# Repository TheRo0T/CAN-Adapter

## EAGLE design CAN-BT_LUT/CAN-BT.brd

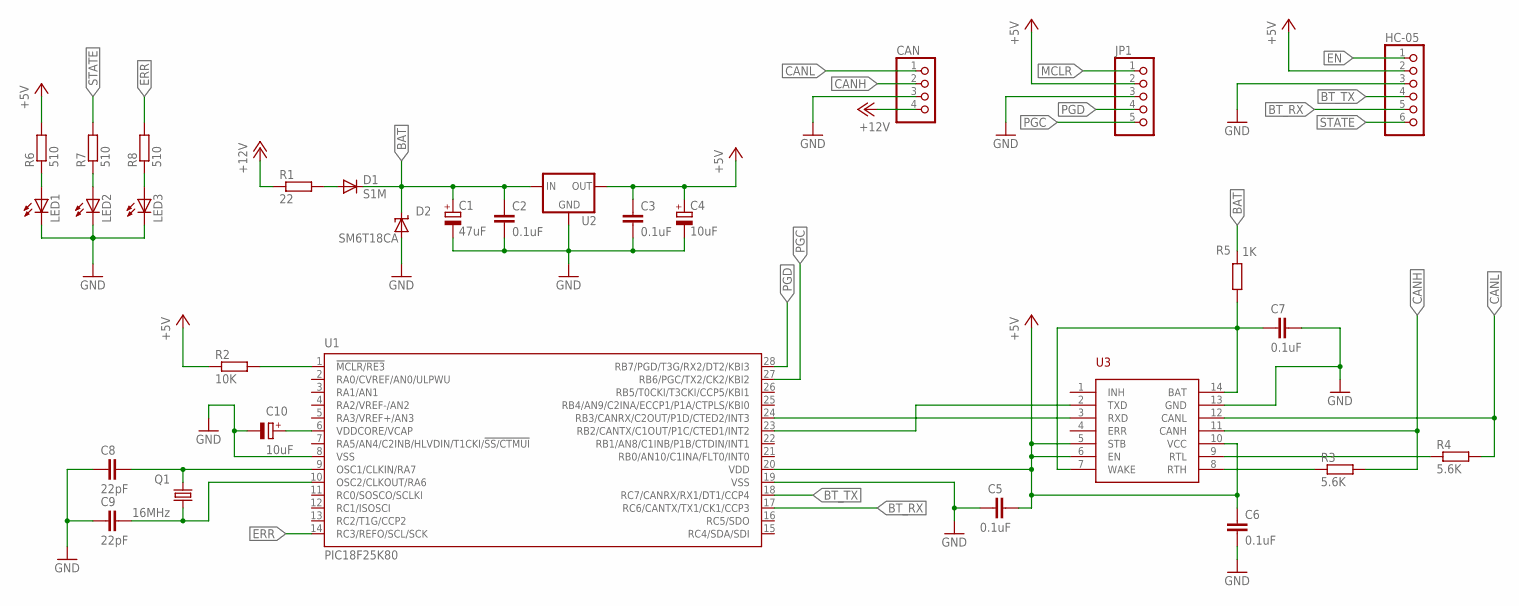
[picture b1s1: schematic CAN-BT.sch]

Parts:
C1: 47uF; 153CLV-0807
C2, C3, C5, C6, C7: 0.1uF; C0805
C4: 10uF; 153CLV-0605
C8, C9: 22pF; C0805
C10: 10uF; SMC_A
CAN: PINHD-1X4; 1X04
D1: S1M; SMA
D2: SM6T18CA; SMBJ
HC-05: PINHD-1X6; 1X06
JP1: PINHD-1X5; 1X05
LED1, LED2, LED3: LEDSQR2X5; LED2X5
Q1: 16MHz; HC49/S
R1: 22; M1206
R2: 10K; R0805
R3, R4: 5.6K; R0805
R5: 1K; R0805
R6, R7, R8: 510; R0805
U1: PIC18F25K80; SO28W
U2: 78M05; DPACK
U3: TJA1055T; SO-14W

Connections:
+5V: C3.1, C4.+, C5.1, C6.1, HC-05.2, JP1.2, R2.1, R6.2, U1.20 (VDD), U2.3 (OUT), U3.5 (STB), U3.6 (EN), U3.10 (VCC)
+12V: CAN.4, R1.1
BAT: C1.+, C2.1, D1.C, D2.C, R5.2, U2.1 (IN)
BT_RX: HC-05.5, U1.17 (RC6/CANTX/TX1/CK1/CCP3)
BT_TX: HC-05.4, U1.18 (RC7/CANRX/RX1/DT1/CCP4)
CANH: CAN.2, R3.2, U3.11 (CANH)
CANL: CAN.1, R4.2, U3.12 (CANL)
EN: HC-05.1
ERR: R8.2, U1.14 (RC3/REFO/SCL/SCK)
GND: C1.-, C2.2, C3.2, C4.-, C5.2, C6.2, C7.2, C8.1, C9.1, C10.-, CAN.3, D2.A, HC-05.3, JP1.3, LED1.K (C), LED2.K (C), LED3.K (C), U1.8 (VSS), U1.19 (VSS), U2.4 (GND), U3.13 (GND)
MCLR: JP1.1
unnamed: D1.A, R1.2
unnamed: U1.23 (RB2/CANTX/C1OUT/P1C/CTED1/INT2), U3.2 (TXD)
unnamed: U1.24 (RB3/CANRX/C2OUT/P1D/CTED2/INT3), U3.3 (RXD)
unnamed: R2.2, U1.1 (!MCLR/RE3)
unnamed: C8.2, Q1.1, U1.9 (OSC1/CLKIN/RA7)
unnamed: C7.1, R5.1, U3.7 (WAKE), U3.14 (BAT)
unnamed: C9.2, Q1.2, U1.10 (OSC2/CLKOUT/RA6)
unnamed: C10.+, U1.6 (VDDCORE/VCAP)
unnamed: LED3.A, R8.1
unnamed: LED1.A, R6.1
unnamed: R3.1, U3.8 (RTH)
unnamed: R4.1, U3.9 (RTL)
unnamed: LED2.A, R7.1
PGC: JP1.5, U1.27 (RB6/PGC/TX2/CK2/KBI2)
PGD: JP1.4, U1.28 (RB7/PGD/T3G/RX2/DT2/KBI3)
STATE: HC-05.6, R7.2

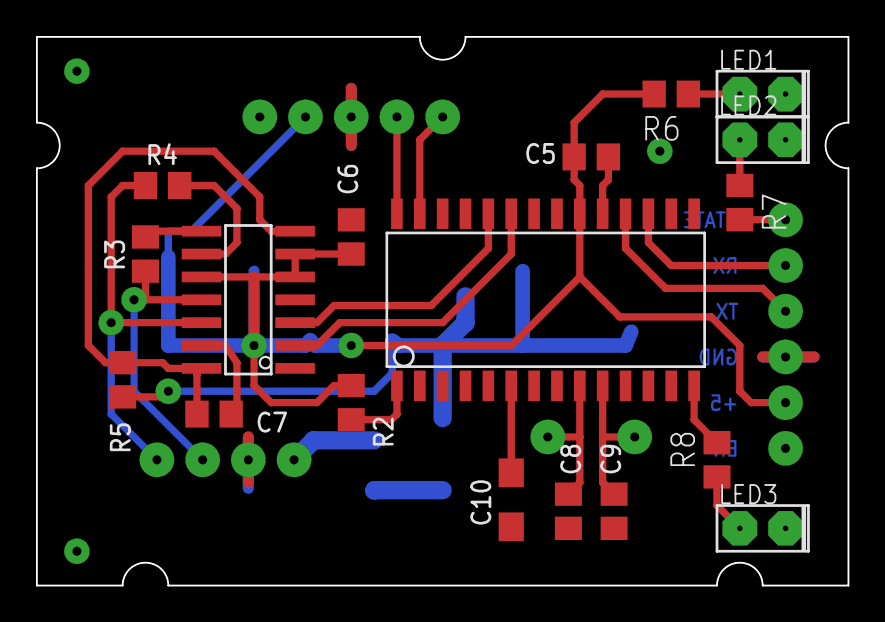
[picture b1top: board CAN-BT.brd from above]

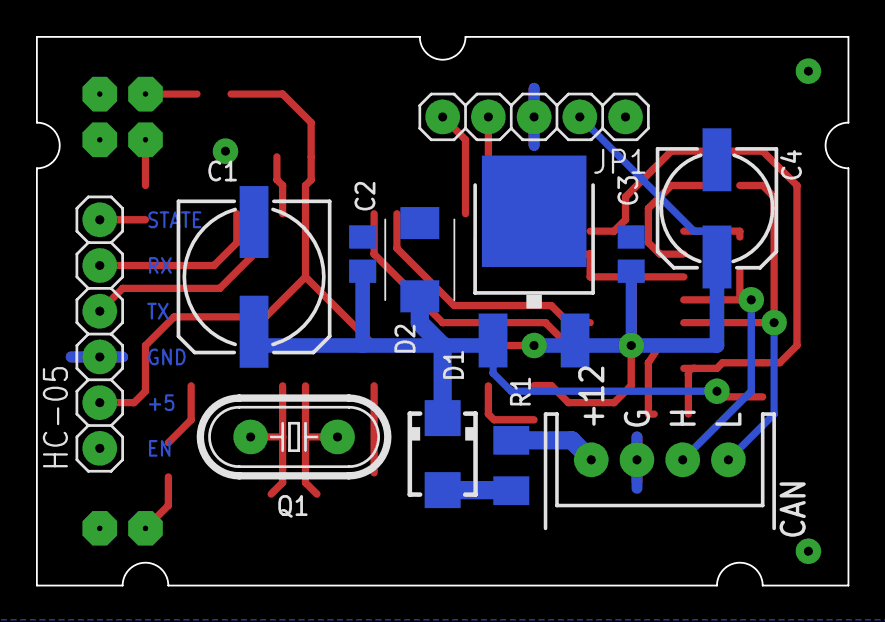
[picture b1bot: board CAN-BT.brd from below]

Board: 2 copper layers, 45.1 x 30.5 mm, 30 parts (12 on the bottom side), 25 nets.

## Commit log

2016-09-02 First
2016-09-07 Add Eagle Project CAN-BT
2016-09-07 Small fix
